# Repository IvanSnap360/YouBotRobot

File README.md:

# OmniBot

Проект для изучения ROS

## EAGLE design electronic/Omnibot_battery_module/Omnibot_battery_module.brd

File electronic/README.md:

# Раздел для проектирования электроники

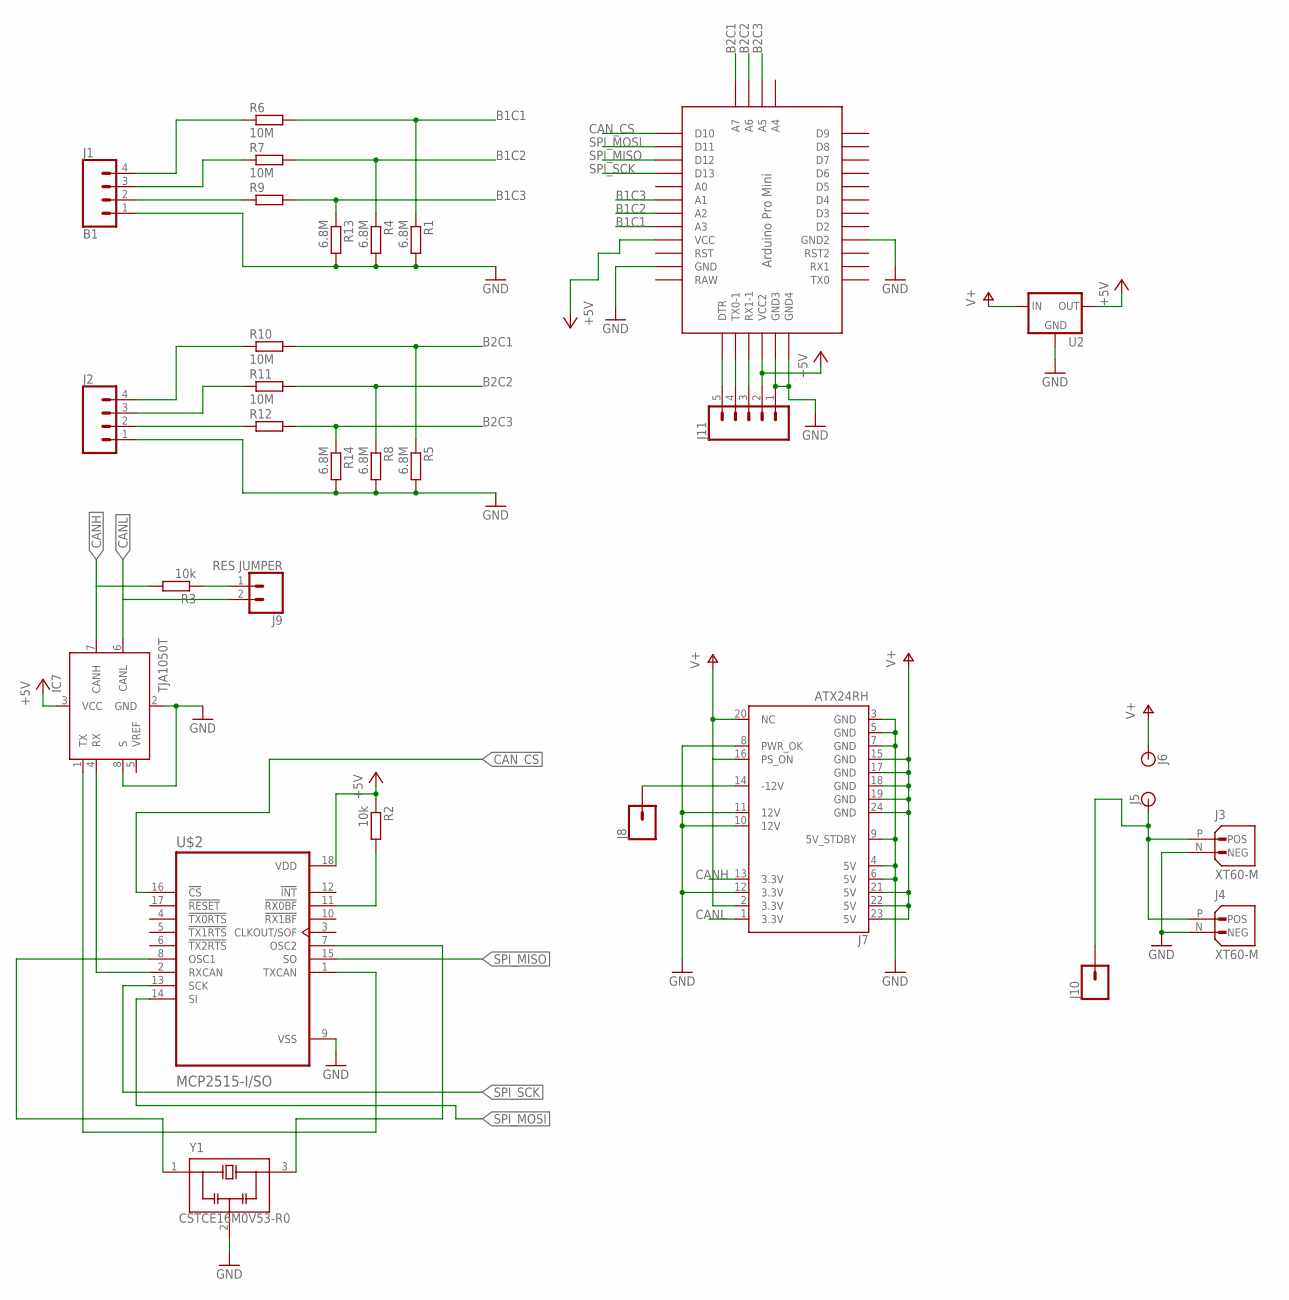
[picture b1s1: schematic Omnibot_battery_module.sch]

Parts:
IC7: TJA1050T; SOIC8
J1: B1; MOLEX-1X4
J2: CONN_04POLAR; MOLEX-1X4
J3, J4: XT60-M; AMASS_XT60-M
J5, J6: BANANA_CONN
J7: ATX24RH; ATX24_RIGHT_ANGLE
J8, J10: CONN_01; 1X01
J9: RES JUMPER; 1X02
J11: CONN_05PTH; 1X05
R1, R4, R5, R8, R13, R14: 6.8M; M0805
R2, R3: 10k; R0805
R6, R7, R9, R10, R11, R12: 10M; M0805
U2: V_REG_78XX-TO-220; TO-220-ALT
U$1: PRO-MINI
U$2: MCP2515-I/SO; SOIC127P1030X265-18N
Y1: CSTCE16M0V53-R0; OSC_CSTCE16M0V53-R0

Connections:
+5V: IC7.3 (VCC), J11.2, R2.1, U2.OUT, U$1.VCC, U$1.VCC1 (VCC2), U$2.18 (VDD)
B1C1: R1.1, R6.2, U$1.A3
B1C2: R4.1, R7.2, U$1.A2
B1C3: R9.2, R13.1, U$1.A1
B2C1: R5.1, R10.2, U$1.A7
B2C2: R8.1, R11.2, U$1.A6
B2C3: R12.2, R14.1, U$1.A5
CANH: IC7.7 (CANH), J7.13 (3.3V), R3.2
CANL: IC7.6 (CANL), J7.1 (3.3V), J9.2
CAN_CS: U$1.D10, U$2.16 (!CS)
GND: IC7.2 (GND), IC7.8 (S), J1.1, J2.1, J3.N (NEG), J4.N (NEG), J7.3 (GND), J7.4 (5V), J7.5 (GND), J7.6 (5V), J7.7 (GND), J7.8 (PWR_OK), J7.9 (5V_STDBY), J7.10 (12V), J7.11 (12V), J7.12 (3.3V), J11.1, R1.2, R4.2, R5.2, R8.2, R13.2, R14.2, U2.GND, U$1.GND, U$1.GND1 (GND2), U$1.GND2 (GND4), U$1.GND3, U$2.9 (VSS), Y1.2 (GND)
unnamed: J7.14 (-12V), J8.1
unnamed: U$2.8 (OSC1), Y1.1 (IN)
unnamed: J3.P (POS), J4.P (POS), J5.P$1, J10.1
unnamed: IC7.4 (RX), U$2.2 (RXCAN)
unnamed: R2.2, U$2.11 (!RX0BF)
unnamed: IC7.1 (TX), U$2.1 (TXCAN)
unnamed: U$2.7 (OSC2), Y1.3 (OUT)
unnamed: J1.4, R6.1
unnamed: J9.1, R3.1
unnamed: J1.3, R7.1
unnamed: J1.2, R9.1
unnamed: J2.4, R10.1
unnamed: J2.3, R11.1
unnamed: J2.2, R12.1
unnamed: J11.3, U$1.RX1-1
unnamed: J11.4, U$1.TX0-1
unnamed: J11.5, U$1.DTR
RAW: U$1.RAW
SPI_MISO: U$1.D12, U$2.15 (SO)
SPI_MOSI: U$1.D11, U$2.14 (SI)
SPI_SCK: U$1.D13, U$2.13 (SCK)
V+: J6.P$1, J7.2 (3.3V), J7.15 (GND), J7.16 (PS_ON), J7.17 (GND), J7.18 (GND), J7.19 (GND), J7.20 (NC), J7.21 (5V), J7.22 (5V), J7.23 (5V), J7.24 (GND), U2.IN

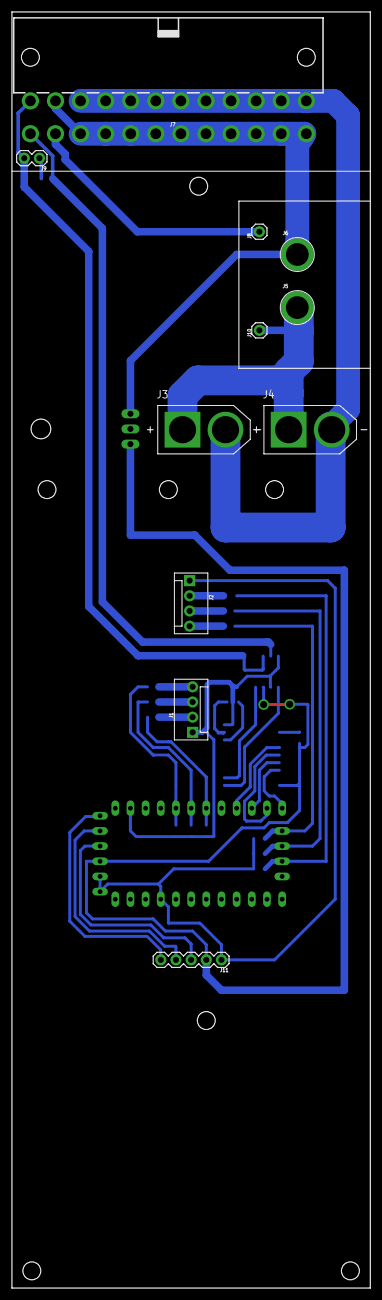
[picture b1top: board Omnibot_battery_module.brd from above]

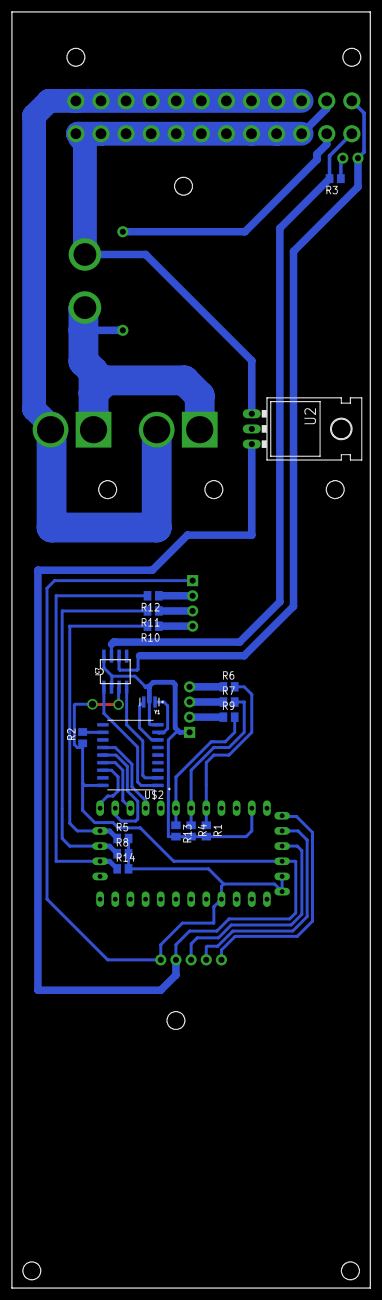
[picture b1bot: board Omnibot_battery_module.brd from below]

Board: 2 copper layers, 60.0 x 213.7 mm, 30 parts (18 on the bottom side), 32 nets.

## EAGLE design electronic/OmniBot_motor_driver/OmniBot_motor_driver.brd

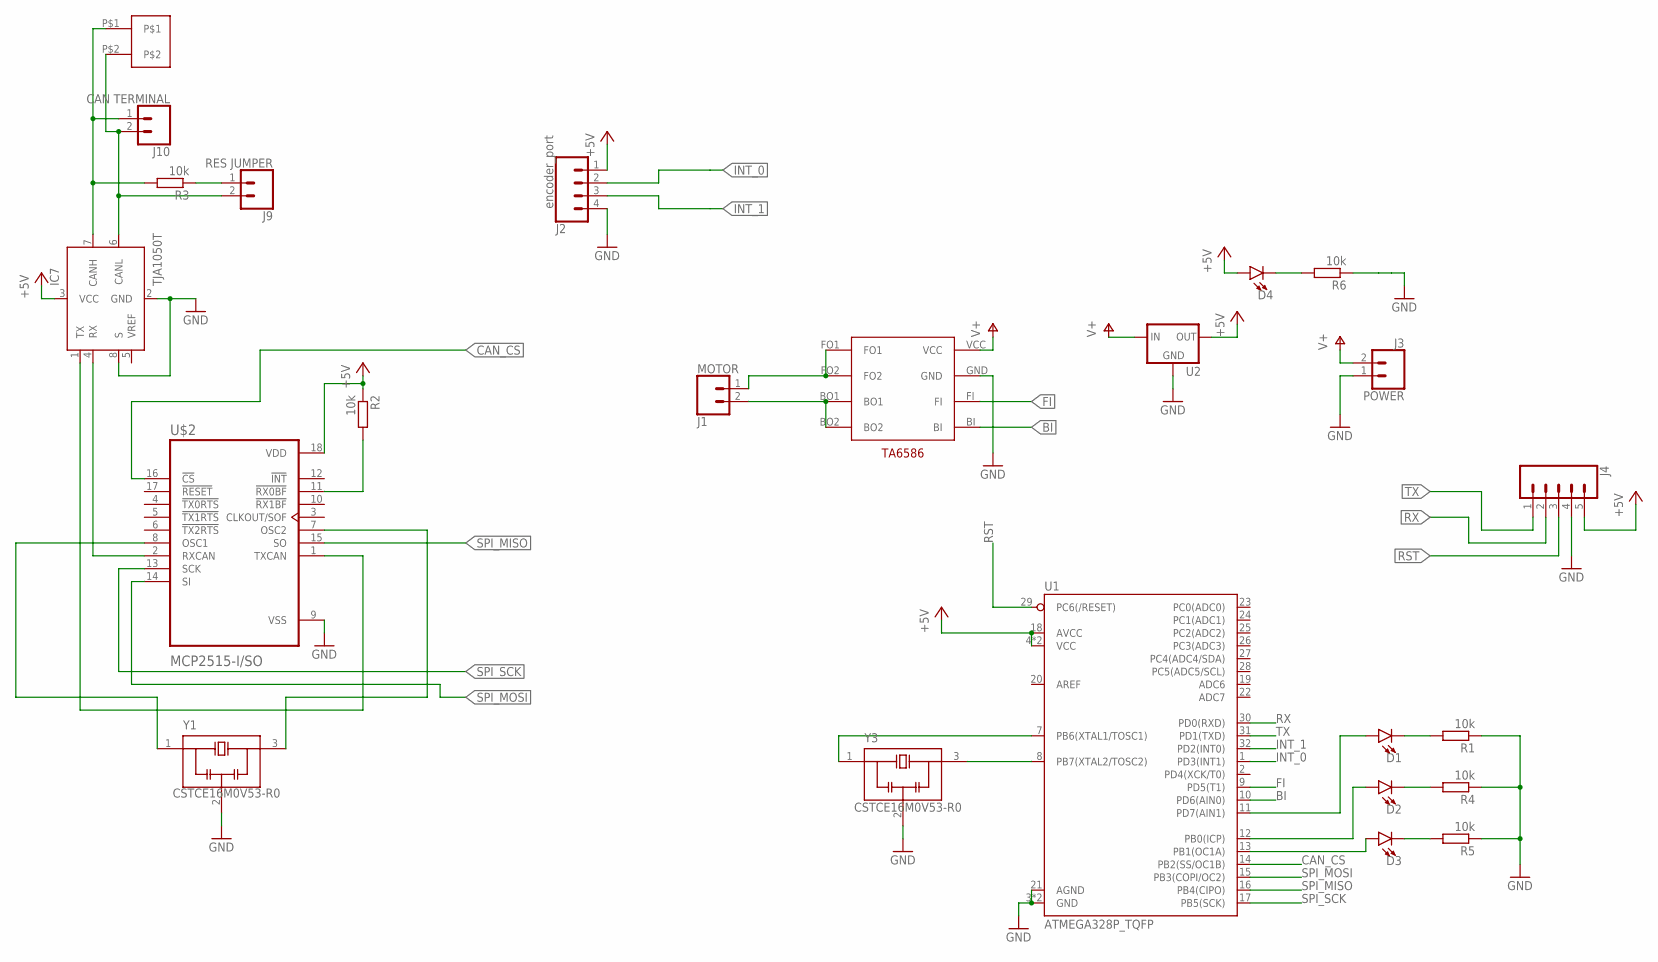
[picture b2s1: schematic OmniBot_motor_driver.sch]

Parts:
D1, D2, D3, D4: LED3MM; LED_3MM
IC7: TJA1050T; SOIC8
J1: MOTOR; SCREWTERMINAL-5MM-2
J2: encoder_port; MOLEX-1X4
J3: POWER; SCREWTERMINAL-5MM-2
J4: CONN_05PTH; 1X05
J9: RES JUMPER; 1X02
J10: CAN TERMINAL; SCREWTERMINAL-5MM-2
R1, R2, R3, R4, R5, R6: 10k; R0805
U1: ATMEGA328P_TQFP; TQFP32-08
U2: V_REG_78XXSINK; TO220-IGO
U$1: 15EDGRC-3.5-2P; 15EDGRC-3.5-2P-PAK
U$2: MCP2515-I/SO; SOIC127P1030X265-18N
U$3: TA6586; TA6586-FOOTPRINT
Y1, Y3: CSTCE16M0V53-R0; OSC_CSTCE16M0V53-R0

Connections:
+5V: D4.A, IC7.3 (VCC), J2.1, J4.5, R2.1, U1.4 (VCC), U1.6 (VCC), U1.18 (AVCC), U2.OUT, U$2.18 (VDD)
BI: U1.10 (PD6(AIN0)), U$3.BI
CAN_CS: U1.14 (PB2(SS/OC1B)), U$2.16 (!CS)
FI: U1.9 (PD5(T1)), U$3.FI
GND: IC7.2 (GND), IC7.8 (S), J2.4, J3.1, J4.4, R1.1, R4.1, R5.1, R6.1, U1.3 (GND), U1.5 (GND), U1.21 (AGND), U2.GND, U$2.9 (VSS), U$3.GND, Y1.2 (GND), Y3.2 (GND)
INT_0: J2.2, U1.1 (PD3(INT1))
INT_1: J2.3, U1.32 (PD2(INT0))
unnamed: U1.8 (PB7(XTAL2/TOSC2)), Y3.3 (OUT)
unnamed: U$2.8 (OSC1), Y1.1 (IN)
unnamed: U1.7 (PB6(XTAL1/TOSC1)), Y3.1 (IN)
unnamed: IC7.1 (TX), U$2.1 (TXCAN)
unnamed: IC7.4 (RX), U$2.2 (RXCAN)
unnamed: R2.2, U$2.11 (!RX0BF)
unnamed: J1.1, U$3.FO1, U$3.FO2
unnamed: J1.2, U$3.BO1, U$3.BO2
unnamed: U$2.7 (OSC2), Y1.3 (OUT)
unnamed: IC7.6 (CANL), J9.2, J10.2, U$1.P$2
unnamed: D1.A, U1.11 (PD7(AIN1))
unnamed: J9.1, R3.1
unnamed: IC7.7 (CANH), J10.1, R3.2, U$1.P$1
unnamed: D2.A, U1.12 (PB0(ICP))
unnamed: D3.A, U1.13 (PB1(OC1A))
unnamed: D1.K (C), R1.2
unnamed: D2.K (C), R4.2
unnamed: D3.K (C), R5.2
unnamed: D4.K (C), R6.2
RST: J4.3, U1.29 (PC6(/RESET))
RX: J4.2, U1.30 (PD0(RXD))
SPI_MISO: U1.16 (PB4(CIPO)), U$2.15 (SO)
SPI_MOSI: U1.15 (PB3(COPI/OC2)), U$2.14 (SI)
SPI_SCK: U1.17 (PB5(SCK)), U$2.13 (SCK)
TX: J4.1, U1.31 (PD1(TXD))
V+: J3.2, U2.IN, U$3.VCC

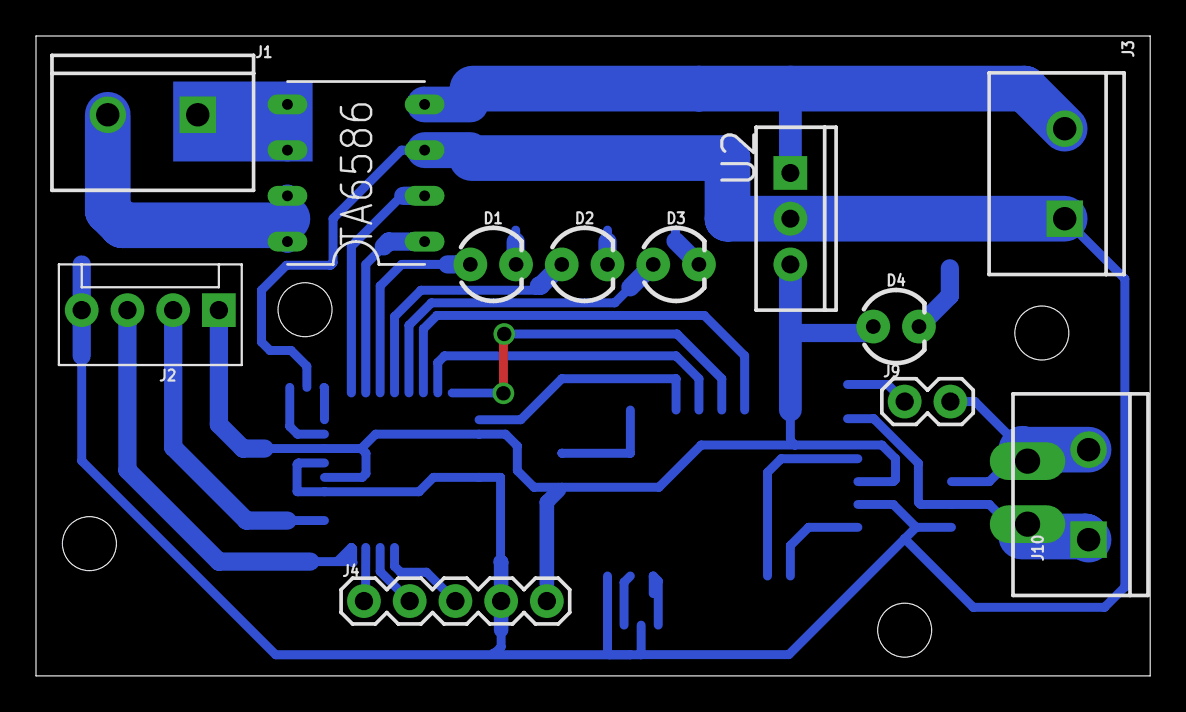
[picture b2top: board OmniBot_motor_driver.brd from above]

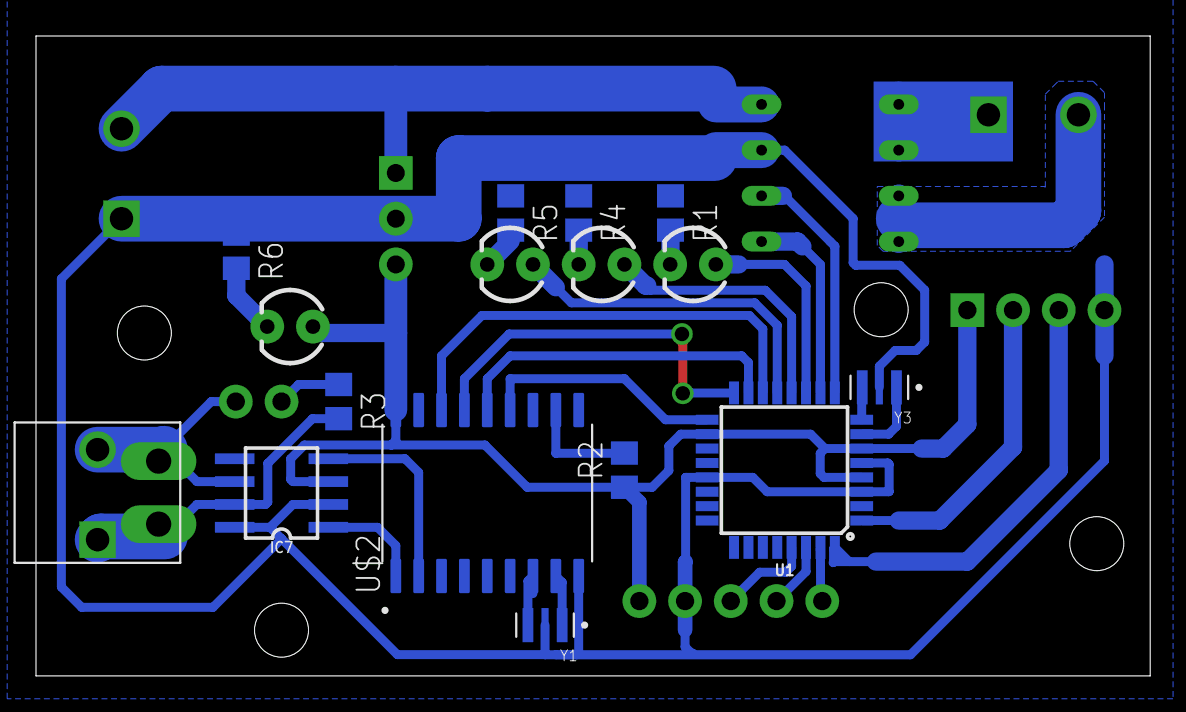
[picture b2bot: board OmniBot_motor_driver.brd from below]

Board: 2 copper layers, 61.9 x 35.5 mm, 24 parts (12 on the bottom side), 33 nets.

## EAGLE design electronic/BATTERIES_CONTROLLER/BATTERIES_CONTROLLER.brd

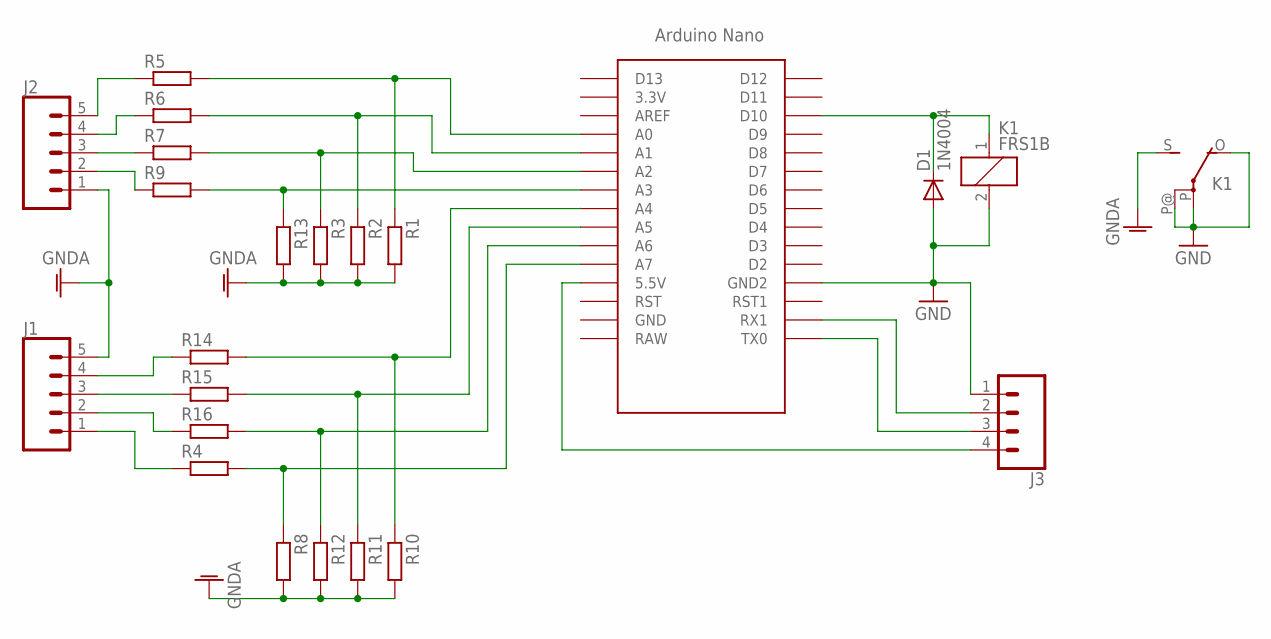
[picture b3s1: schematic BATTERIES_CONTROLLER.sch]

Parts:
D1: 1N4004; DO41-10
J1, J2: CONN_05; 1X05
J3: CONN_04; 1X04
K1: FRS1B
R1, R2, R3, R4, R5, R6, R7, R8, R9, R10, R11, R12, R13, R14, R15, R16: R-EU_M0805; M0805
U$1: NANO

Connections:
GND: D1.A, J3.1, K1.2, K1.O, K1.P, K1.P@, U$1.GND1 (GND2)
GNDA: J1.5, J2.1, K1.S, R1.2, R2.2, R3.2, R8.2, R10.2, R11.2, R12.2, R13.2
unnamed: R1.1, R5.2, U$1.A0
unnamed: R2.1, R6.2, U$1.A1
unnamed: R3.1, R7.2, U$1.A2
unnamed: R4.2, R8.1, U$1.A7
unnamed: J2.5, R5.1
unnamed: J2.4, R6.1
unnamed: J2.3, R7.1
unnamed: D1.C, K1.1, U$1.D10
unnamed: J1.1, R4.1
unnamed: R10.1, R14.2, U$1.A4
unnamed: R11.1, R15.2, U$1.A5
unnamed: R12.1, R16.2, U$1.A6
unnamed: R9.2, R13.1, U$1.A3
unnamed: J1.4, R14.1
unnamed: J1.3, R15.1
unnamed: J1.2, R16.1
unnamed: J2.2, R9.1
unnamed: J3.2, U$1.RX1
unnamed: J3.3, U$1.TX0
unnamed: J3.4, U$1.5V (5.5V)

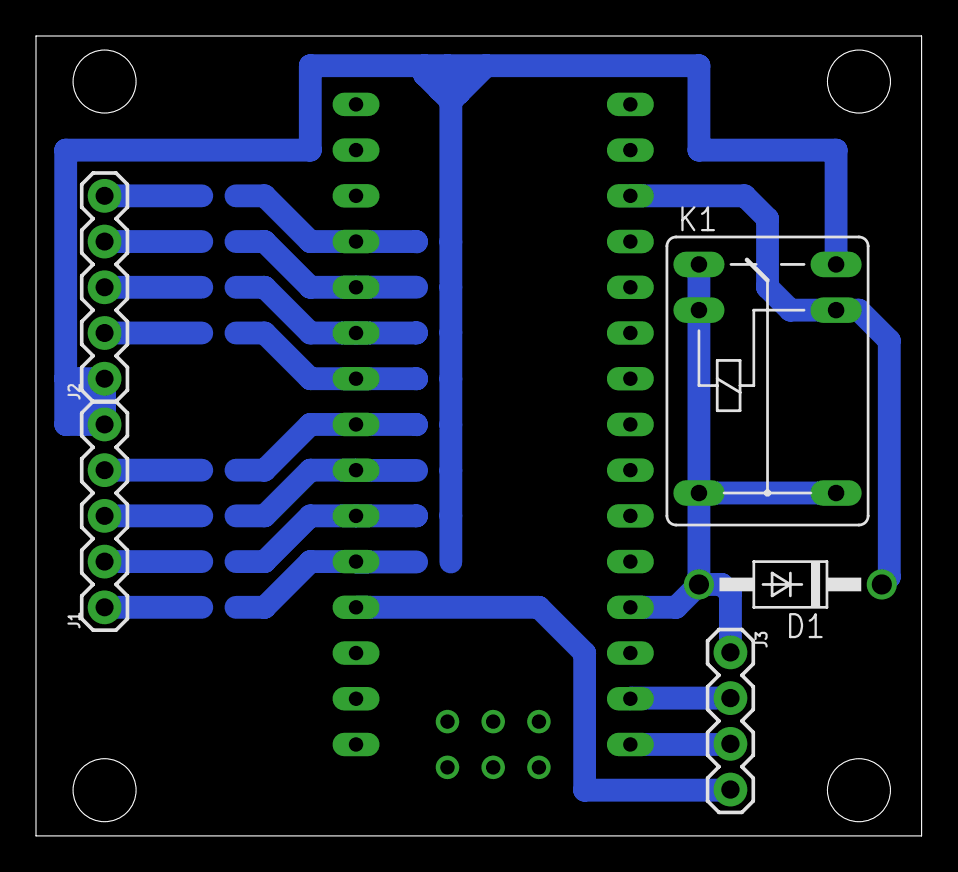
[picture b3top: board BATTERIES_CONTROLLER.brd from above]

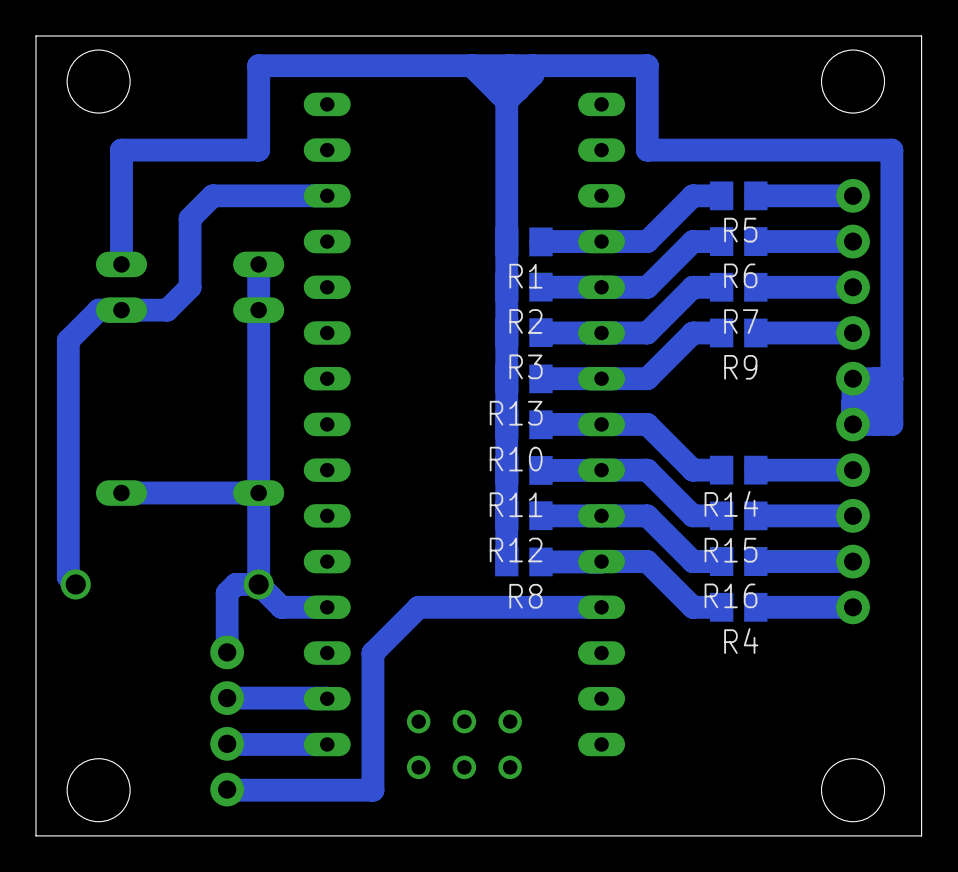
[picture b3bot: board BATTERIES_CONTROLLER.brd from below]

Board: 2 copper layers, 49.2 x 44.4 mm, 22 parts (16 on the bottom side), 22 nets.

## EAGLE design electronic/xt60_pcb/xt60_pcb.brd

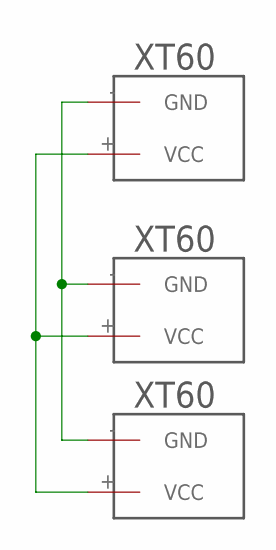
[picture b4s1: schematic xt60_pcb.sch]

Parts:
U$1, U$2, U$3: XT60

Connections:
unnamed: U$1.+ (VCC), U$2.+ (VCC), U$3.+ (VCC)
unnamed: U$1.- (GND), U$2.- (GND), U$3.- (GND)

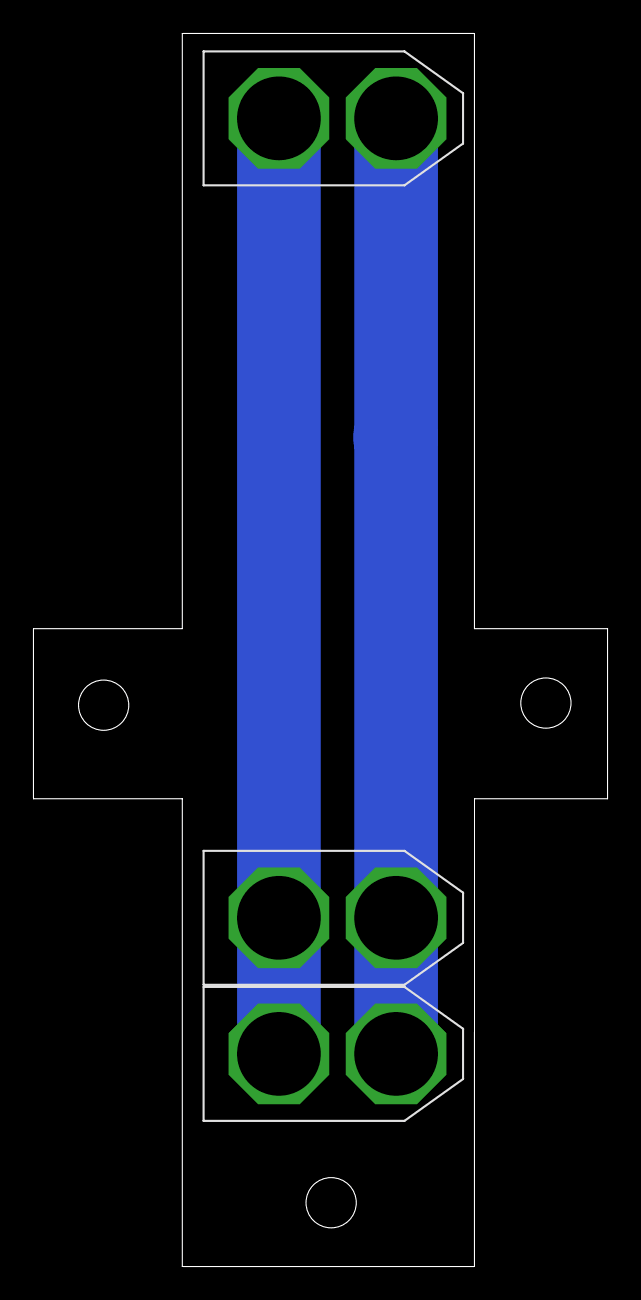
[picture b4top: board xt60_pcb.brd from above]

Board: 2 copper layers, 34.3 x 73.7 mm, 3 parts (0 on the bottom side), 2 nets.

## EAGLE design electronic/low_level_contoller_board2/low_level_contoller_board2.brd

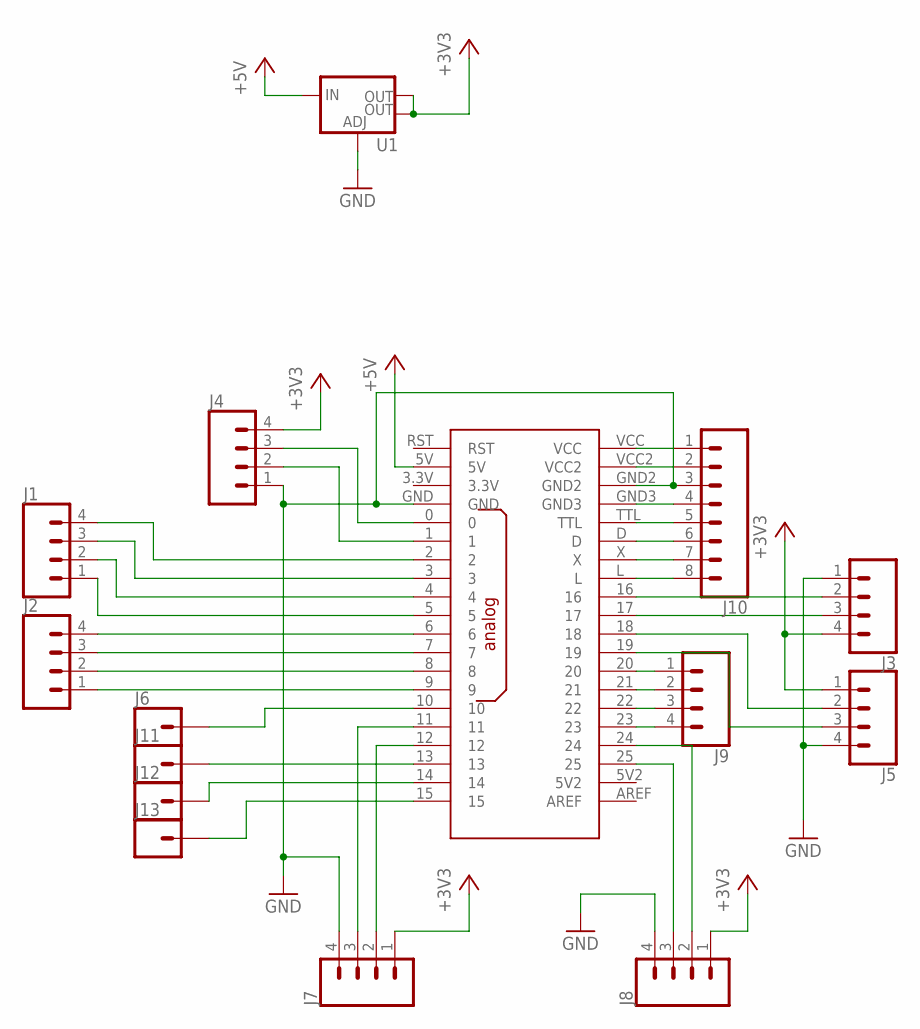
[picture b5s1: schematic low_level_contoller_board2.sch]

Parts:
J1, J2: CONN_04POLAR; MOLEX-1X4
J3, J4, J5, J7, J8, J9: CONN_04; 1X04
J6, J11, J12, J13: CONN_01; 1X01
J10: CONN_08"; 1X08
U1: V_REG_LM1117SOT223; SOT223
U$1: OPENCM9.04

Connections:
+3V3: J3.4, J4.4, J5.1, J7.1, J8.1, U1.2 (OUT), U1.4 (OUT)
+5V: U1.3 (IN), U$1.5V
GND: J3.1, J4.1, J5.4, J7.4, J8.4, J10.3, U1.1 (ADJ), U$1.GND, U$1.GND2
unnamed: J1.4, U$1.2
unnamed: J1.3, U$1.3
unnamed: J1.2, U$1.4
unnamed: J1.1, U$1.5
unnamed: J2.4, U$1.6
unnamed: J2.3, U$1.7
unnamed: J2.2, U$1.8
unnamed: J2.1, U$1.9
unnamed: J3.2, U$1.16
unnamed: J3.3, U$1.17
unnamed: J5.2, U$1.18
unnamed: J5.3, U$1.19
unnamed: J4.3, U$1.0
unnamed: J4.2, U$1.1
unnamed: J6.1, U$1.10
unnamed: J11.1, U$1.13
unnamed: J7.3, U$1.11
unnamed: J7.2, U$1.12
unnamed: J9.1, U$1.20
unnamed: J8.3, U$1.25
unnamed: J8.2, U$1.24
unnamed: J9.2, U$1.21
unnamed: J9.3, U$1.22
unnamed: J9.4, U$1.23
unnamed: J10.1, U$1.VCC
unnamed: J10.2, U$1.VCC2
unnamed: J12.1, U$1.14
unnamed: J10.4, U$1.GND3
unnamed: J10.5, U$1.TTL
unnamed: J10.6, U$1.D
unnamed: J10.7, U$1.X
unnamed: J10.8, U$1.L
unnamed: J13.1, U$1.15

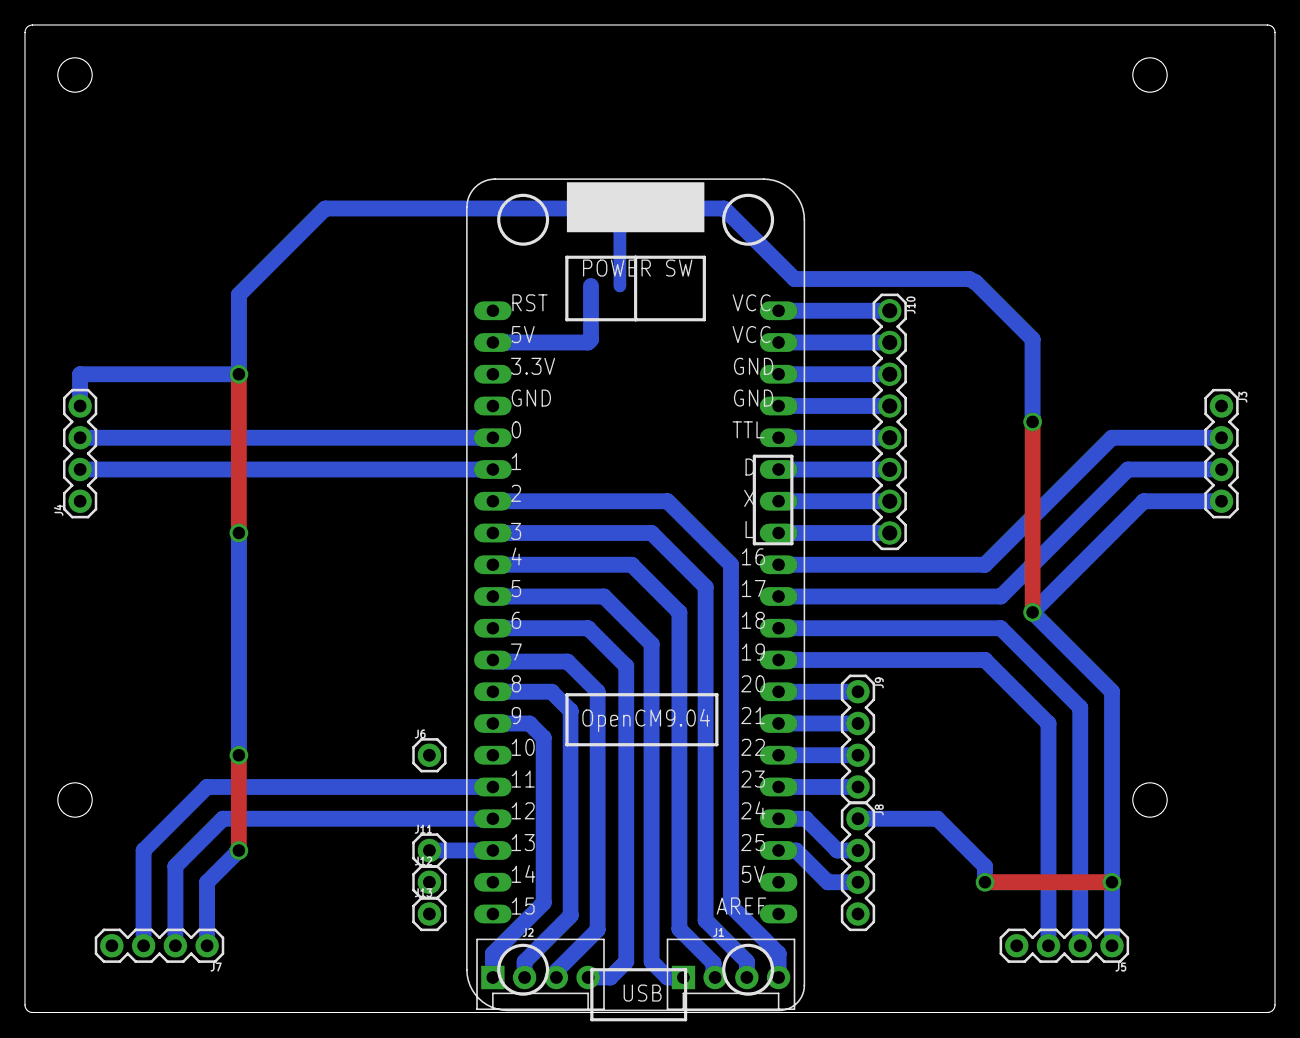
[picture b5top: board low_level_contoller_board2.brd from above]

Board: 2 copper layers, 100.0 x 79.0 mm, 15 parts (1 on the bottom side), 36 nets.

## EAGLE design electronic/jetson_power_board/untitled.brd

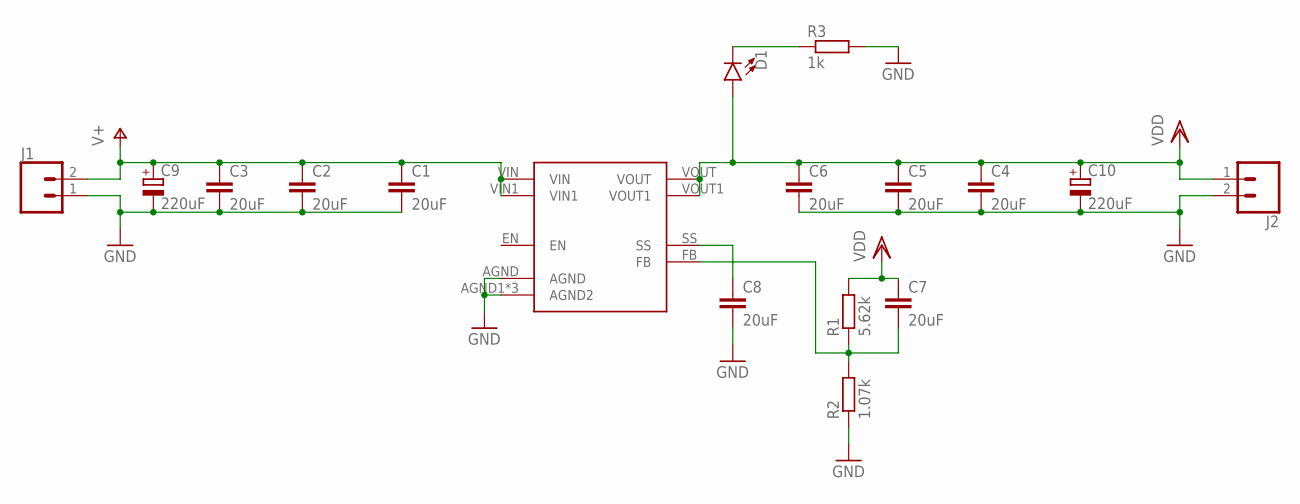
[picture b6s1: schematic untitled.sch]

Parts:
C1, C2, C3, C4, C5, C6, C7, C8: 20uF; C0805K
C9, C10: 220uF; 153CLV-0810
D1: LED5MM; LED_5MM
J1, J2: CONN_025MM; SCREWTERMINAL-5MM-2
R1: 5.62k; R0805
R2: 1.07k; R0805
R3: 1k; R0805
U$1: LMZ13610

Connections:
GND: C1.2, C2.2, C3.2, C4.2, C5.2, C6.2, C8.2, C9.-, C10.-, J1.1, J2.2, R2.1, R3.2, U$1.AGND, U$1.AGND1 (AGND2), U$1.AGND2, U$1.AGND3 (AGND2)
unnamed: C8.1, U$1.SS
unnamed: C7.2, R1.1, R2.2, U$1.FB
unnamed: D1.K (C), R3.1
V+: C1.1, C2.1, C3.1, C9.+, J1.2, U$1.VIN, U$1.VIN1
VDD: C4.1, C5.1, C6.1, C7.1, C10.+, D1.A, J2.1, R1.2, U$1.VOUT, U$1.VOUT1

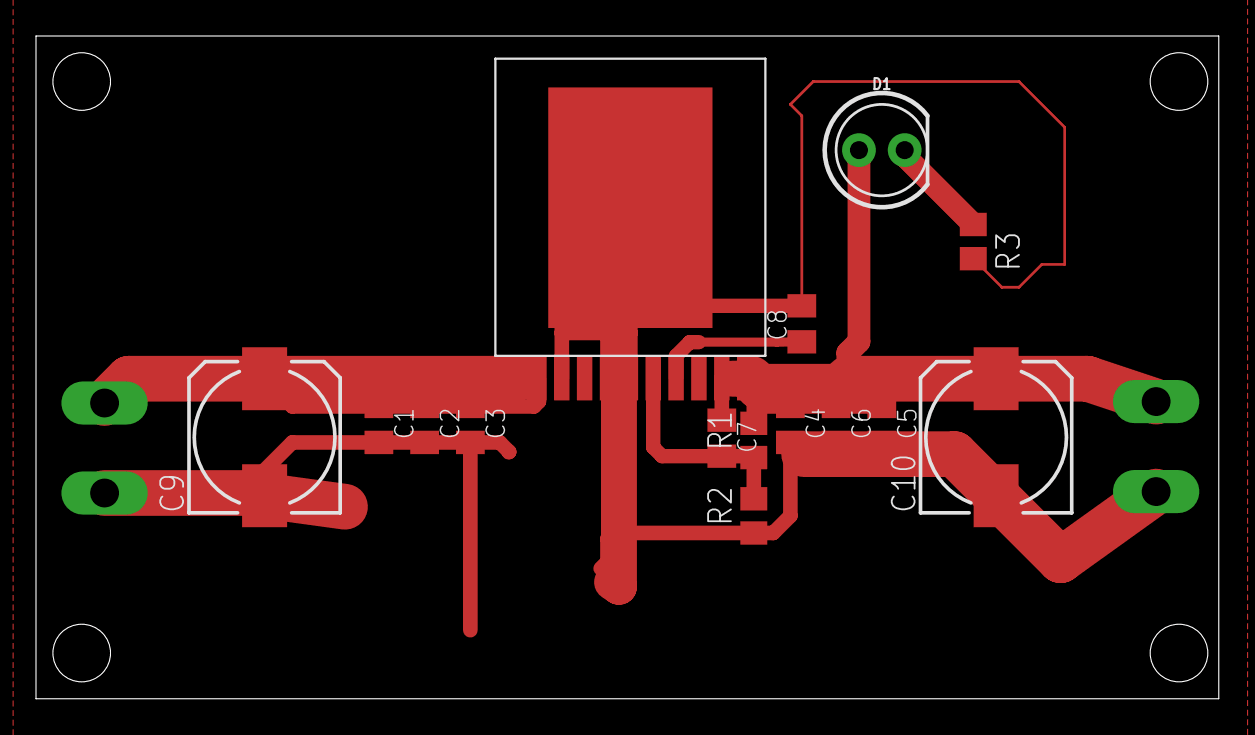
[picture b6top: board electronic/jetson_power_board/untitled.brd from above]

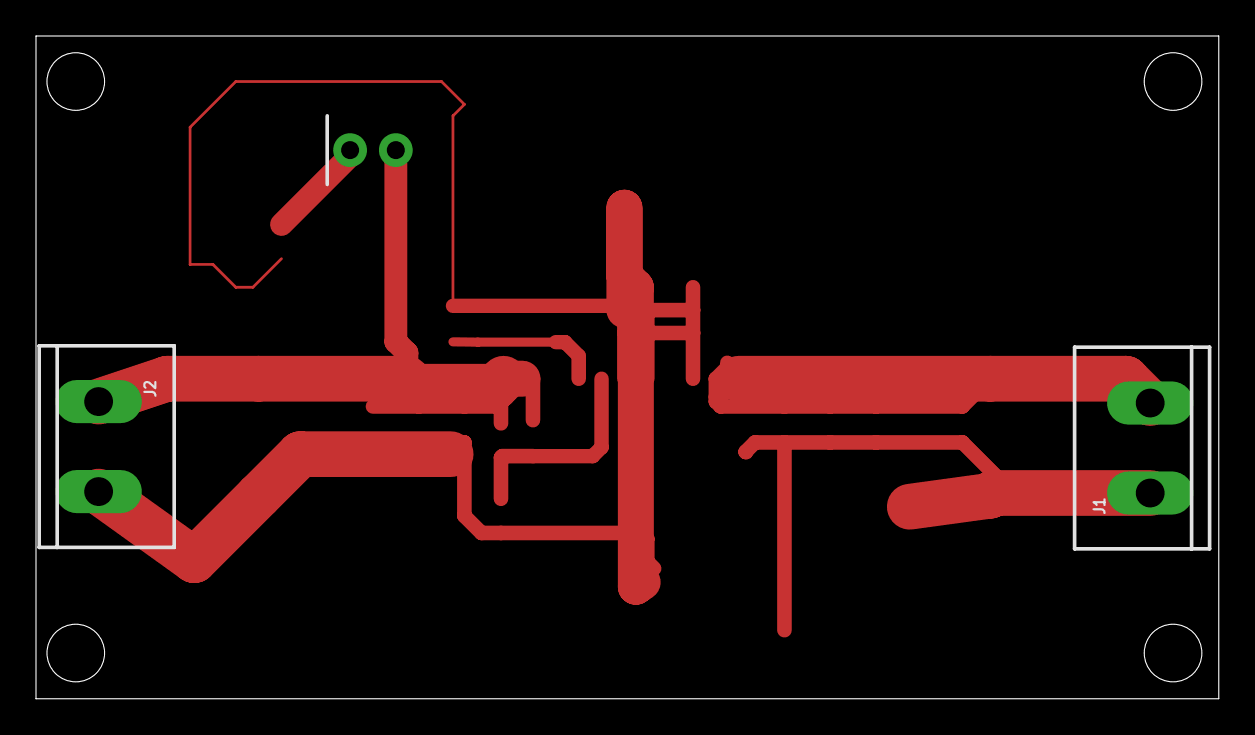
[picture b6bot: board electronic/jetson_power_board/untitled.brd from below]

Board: 2 copper layers, 65.7 x 36.8 mm, 17 parts (2 on the bottom side), 6 nets.

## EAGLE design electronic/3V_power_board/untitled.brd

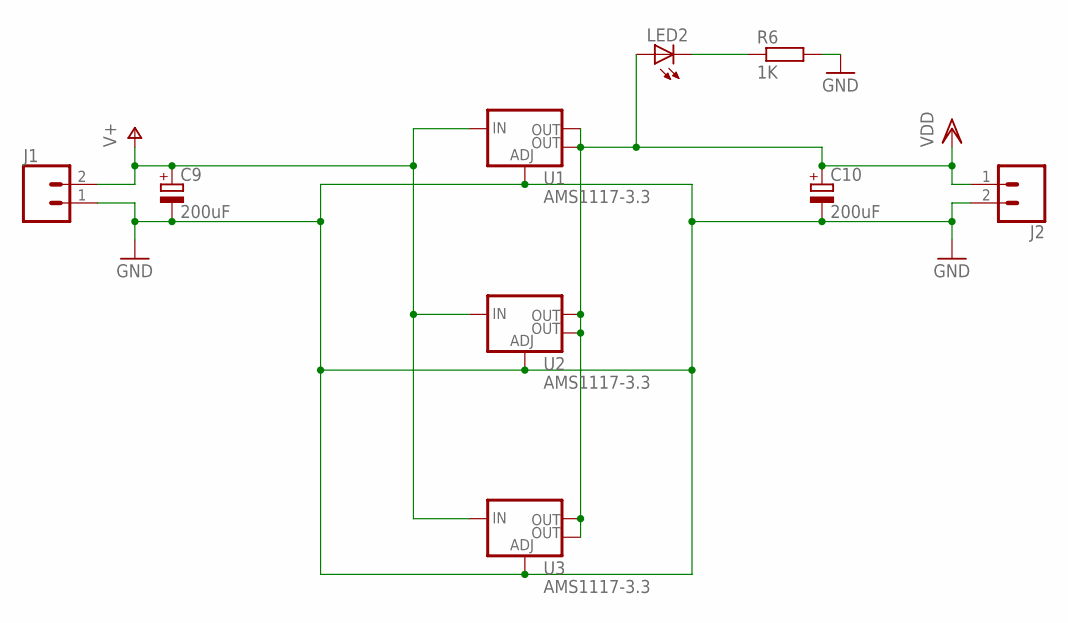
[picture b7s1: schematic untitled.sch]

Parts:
C9, C10: 200uF; 153CLV-0810
J1, J2: CONN_025MM; SCREWTERMINAL-5MM-2
LED2: LED5MM
R6: 1K; R0805
U1, U2, U3: AMS1117-3.3; SOT223

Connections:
GND: C9.-, C10.-, J1.1, J2.2, R6.2, U1.1 (ADJ), U2.1 (ADJ), U3.1 (ADJ)
unnamed: LED2.K (C), R6.1
V+: C9.+, J1.2, U1.3 (IN), U2.3 (IN), U3.3 (IN)
VDD: C10.+, J2.1, LED2.A, U1.2 (OUT), U1.4 (OUT), U2.2 (OUT), U2.4 (OUT), U3.2 (OUT), U3.4 (OUT)

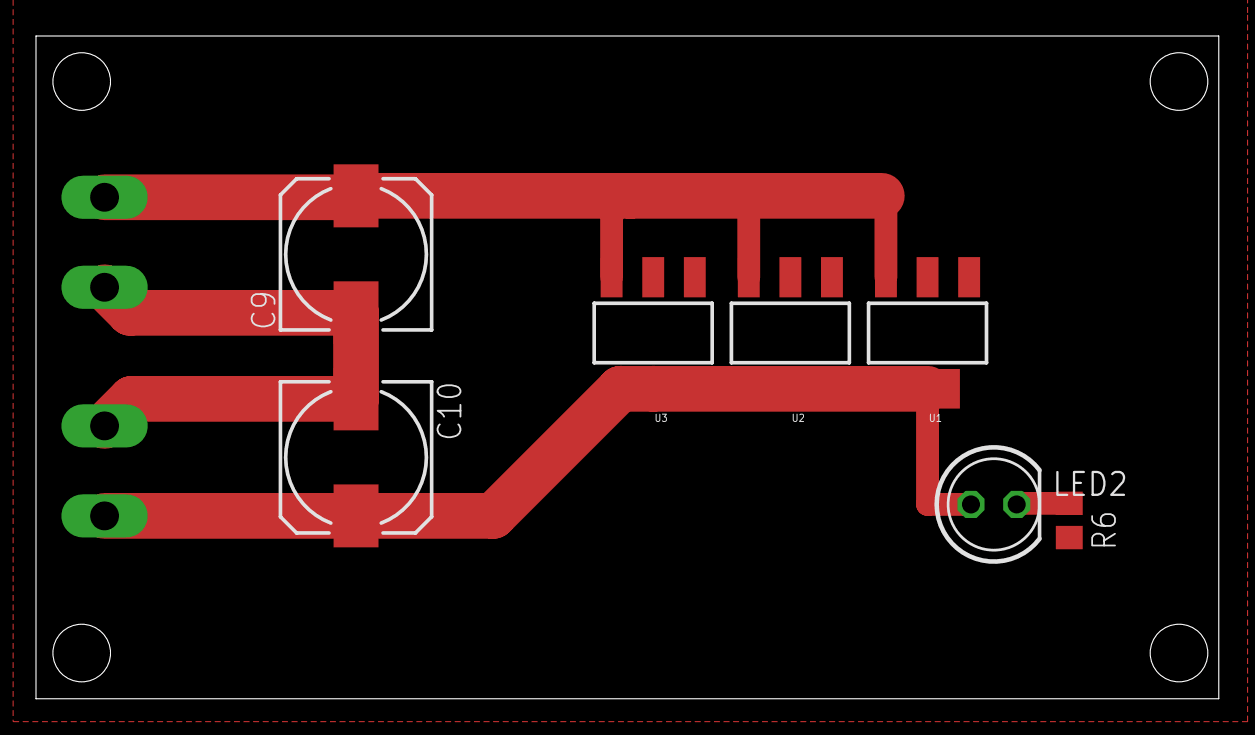
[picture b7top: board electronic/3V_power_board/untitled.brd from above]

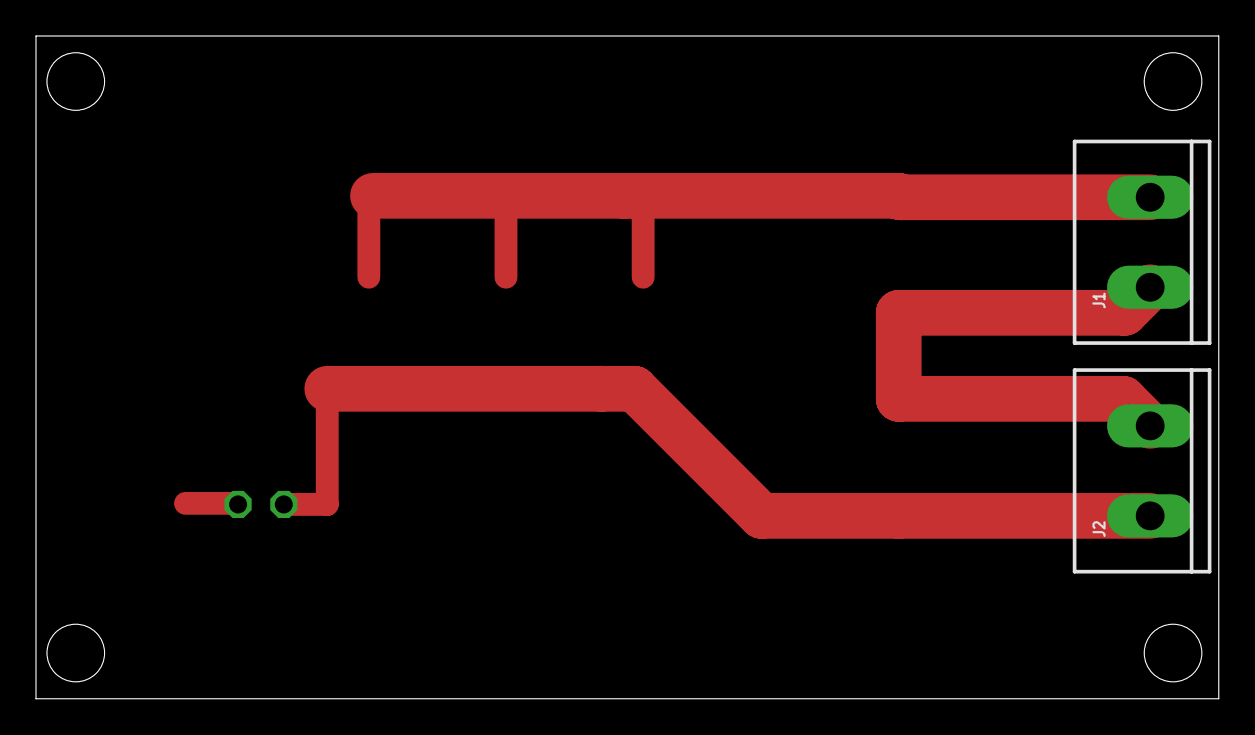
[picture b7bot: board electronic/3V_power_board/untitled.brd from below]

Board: 2 copper layers, 65.7 x 36.8 mm, 9 parts (2 on the bottom side), 4 nets.

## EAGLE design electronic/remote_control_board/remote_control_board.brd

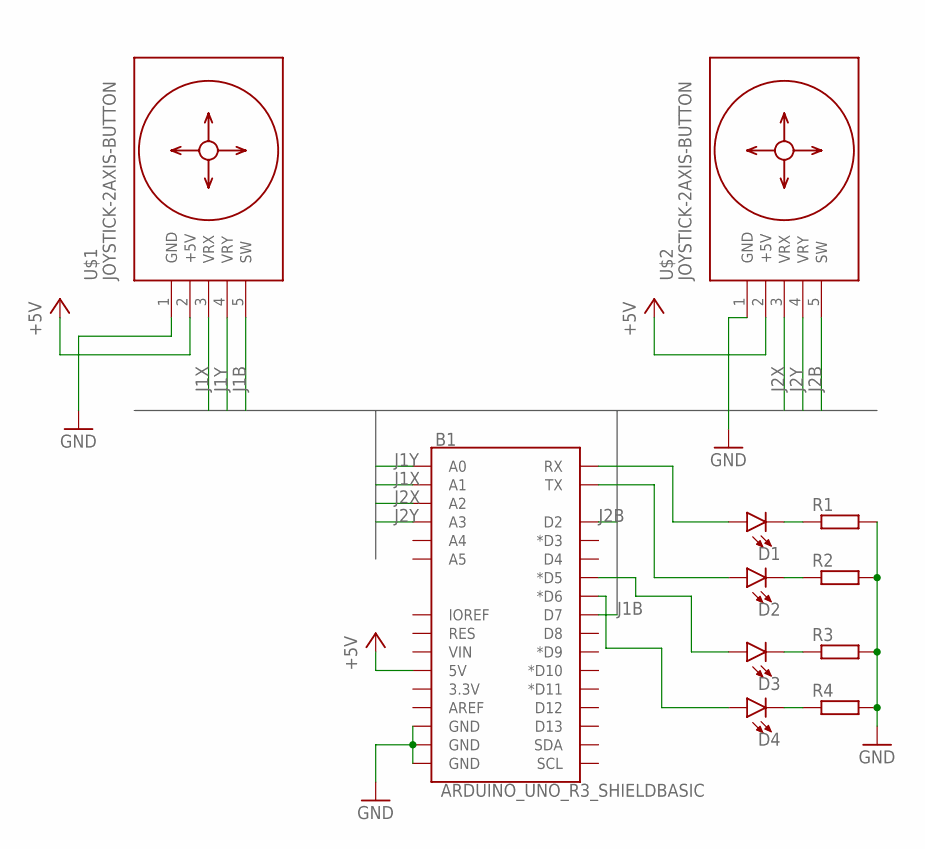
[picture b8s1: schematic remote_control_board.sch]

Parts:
B1: ARDUINO_UNO_R3_SHIELDBASIC; UNO_R3_SHIELD
D1, D2, D3, D4: LED5MM; LED_5MM
R1, R2, R3, R4: R-EU_0204/7; 0204/7
U$1, U$2: JOYSTICK-2AXIS-BUTTON

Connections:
+5V: B1.5V, U$1.2 (+5V), U$2.2 (+5V)
GND: B1.GND@0 (GND), B1.GND@2 (GND), R1.2, R2.2, R3.2, R4.2, U$1.1 (GND), U$2.1 (GND)
J1B: B1.D7, U$1.5 (SW)
J1X: B1.A1, U$1.3 (VRX)
J1Y: B1.A0, U$1.4 (VRY)
J2B: B1.D2, U$2.5 (SW)
J2X: B1.A2, U$2.3 (VRX)
J2Y: B1.A3, U$2.4 (VRY)
unnamed: B1.RX, D1.A
unnamed: B1.TX, D2.A
unnamed: D1.K (C), R1.1
unnamed: D2.K (C), R2.1
unnamed: D3.K (C), R3.1
unnamed: D4.K (C), R4.1
unnamed: B1.D5 (*D5), D3.A
unnamed: B1.D6 (*D6), D4.A

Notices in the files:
parts and their libraries:
SparkFun-Connectors: Licensing: Creative Commons ShareAlike 4.0 International - https://creativecommons.org/licenses/by-sa/4.0
diy-modules: Released under the Creative Commons Attribution 4.0 International License: http://creativecommons.org/licenses/by/4.0
